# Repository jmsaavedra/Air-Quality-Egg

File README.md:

# Air Quality Egg

A large-scale distributed air quality network sensor device. based on the Nanode
an Arduino-compatible, Ethernet enabled microcontroller.
[airqualityegg.com](http://airqualityegg.com)

## Sensors
* temp/humidity (RHT22)
* carbon monoxide (e2v MICS-5525)
* nitrous dioxide (e2v MICS-2710)

## Notes
* auto reset feature connects digitalPin 3 to RESET pin
** this *must* be disconnected when programming the board.

## Collaborators
* [cosm.com](http://cosm.com)
* [citizensensor.cc](http://citizensensor.cc) | [jos.ph](http://jos.ph)
* [Wicked Device](http://wickeddevice.com)
* Ricardo Piedrahita, Nick Masson - UC Boulder (-link-)
* your name here

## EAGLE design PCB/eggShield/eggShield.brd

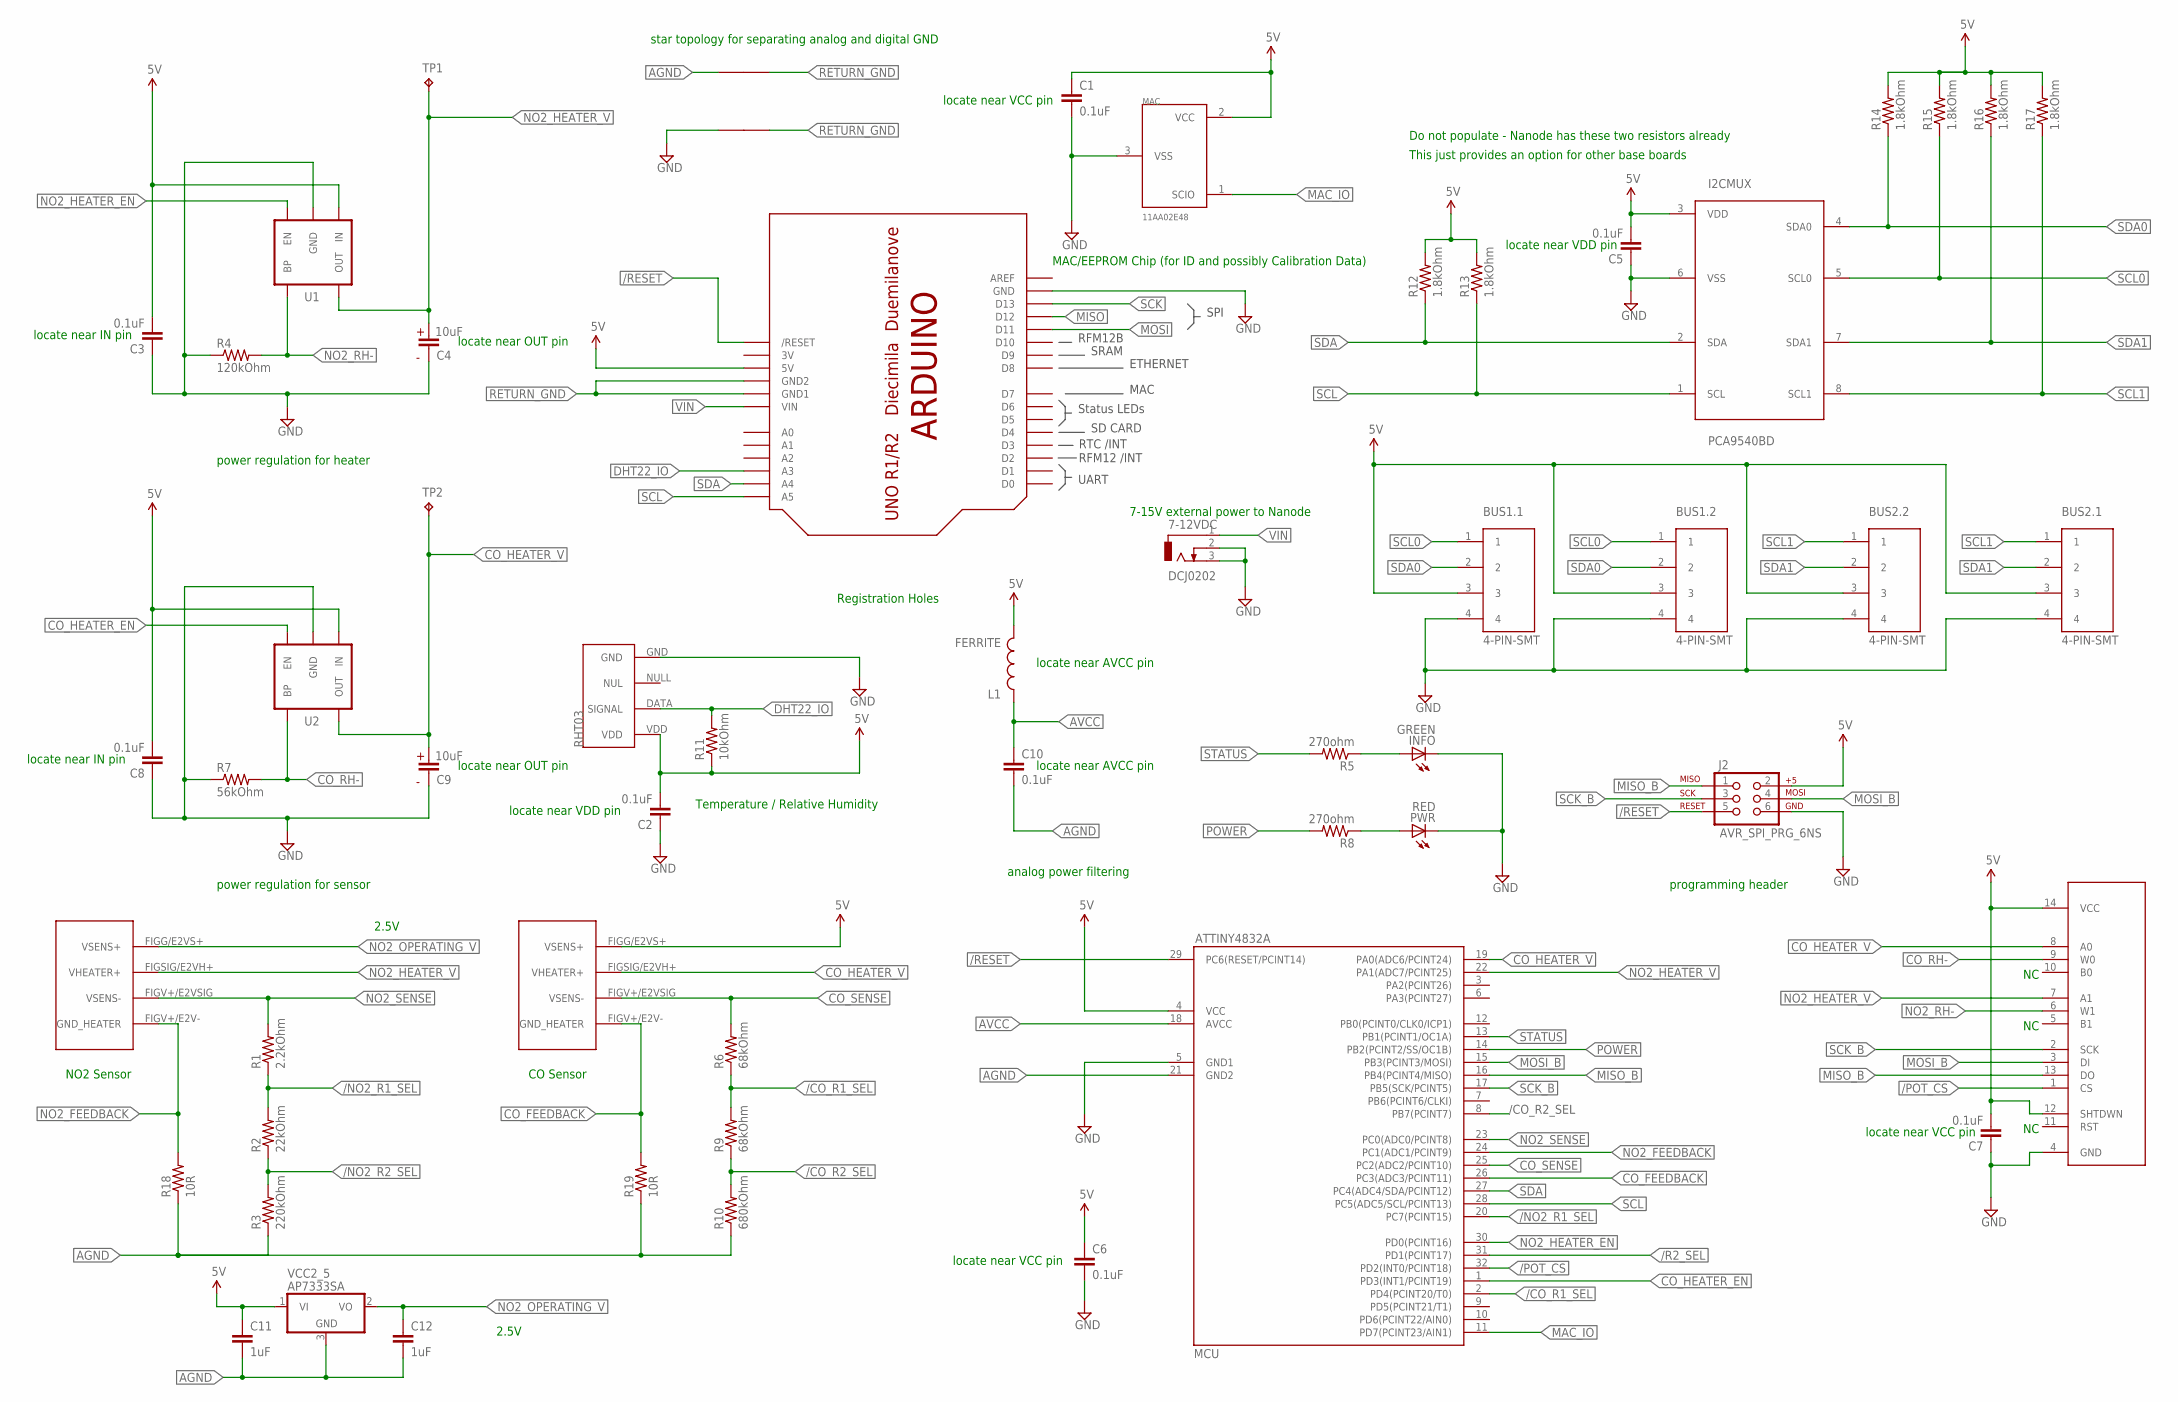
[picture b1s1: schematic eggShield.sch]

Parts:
7-12VDC: DCJ0202
BUS1.1, BUS1.2, BUS2.1, BUS2.2: 4-PIN-SMT; 1775470-4
C1, C2, C3, C5, C6, C7, C8, C10: 0.1uF; 0805
C4, C9: 10uF; TYPE-B_ALUMINUM_CAN
C11, C12: 1uF; 0805
CO: E2V; SR-4
DHT22: RHT03; 1X04_LOCK
I2CMUX: PCA9540BD; SO8
INFO: GREEN; CHIPLED_0805
J2: AVR_SPI_PRG_6NS; 2X3-NS
L1: FERRITE; 0805
MAC: 11AA02E48; SOT23
MCU: ATTINY4832A; TQFP32-08
N02: E2V; SR-4
PWR: RED; CHIPLED_0805
R1: 2.2kOhm; 0805
R2: 22kOhm; 0805
R3: 220kOhm; 0805
R4: 120kOhm; 0805
R5, R8: 270ohm; 0805
R6, R9: 68kOhm; 0805
R7: 56kOhm; 0805
R10: 680kOhm; 0805
R11: 10kOhm; 0805
R12, R13, R14, R15, R16, R17: 1.8kOhm; 0805
R18, R19: 10R; 0805
TP1, TP2: TPPAD1-13; P1-13
U1, U2: V_REG_LDOSMD; SOT23-5
U3: MCP42XXX; SO014
U$7: ARDUINO-NOHOLE
U$13, U$14: PLANE_COUPLER
VCC2_5: AP7333SA; SOT-23-3

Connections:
3V: U$7.3V
5V: BUS1.1.3, BUS1.2.3, BUS2.1.3, BUS2.2.3, C1.1, C2.2, C3.2, C5.2, C6.1, C7.2, C8.2, C11.1, CO.FIGG/E2VS+ (VSENS+), DHT22.VDD, I2CMUX.3 (VDD), J2.2, L1.2, MAC.2 (VCC), MCU.4 (VCC), R11.1, R12.2, R13.2, R14.2, R15.2, R16.2, R17.2, U1.1 (IN), U2.1 (IN), U3.12 (SHTDWN), U3.14 (VCC), U$7.5V, VCC2_5.1 (VI)
/CO_R1_SEL: MCU.2 (PD4(PCINT20/T0)), R6.1, R9.2
/CO_R2_SEL: MCU.8 (PB7(PCINT7)), R9.1, R10.2
/NO2_R1_SEL: MCU.20 (PC7(PCINT15)), R1.1, R2.2
/NO2_R2_SEL: R2.1, R3.2
/POT_CS: MCU.32 (PD2(INT0/PCINT18)), U3.1 (CS)
/R2_SEL: MCU.31 (PD1(PCINT17))
/RESET: J2.5, MCU.29 (PC6(RESET/PCINT14)), U$7.RESET (/RESET)
AGND: C10.2, C11.2, C12.2, MCU.21 (GND2), R3.1, R10.1, R18.1, R19.1, U$13.1, VCC2_5.3 (GND)
AVCC: C10.1, L1.1, MCU.18 (AVCC)
CO_FEEDBACK: CO.FIGV+/E2V- (GND_HEATER), MCU.26 (PC3(ADC3/PCINT11)), R19.2
CO_HEATER_EN: MCU.1 (PD3(INT1/PCINT19)), U2.3 (EN)
CO_HEATER_V: C9.P$1 (1), CO.FIGSIG/E2VH+ (VHEATER+), MCU.19 (PA0(ADC6/PCINT24)), TP2.TP, U2.5 (OUT), U3.8 (A0)
CO_RH-: R7.2, U2.4 (BP), U3.9 (W0)
CO_SENSE: CO.FIGV+/E2VSIG (VSENS-), MCU.25 (PC2(ADC2/PCINT10)), R6.2
DHT22_IO: DHT22.DATA (SIGNAL), R11.2, U$7.A3
GND: 7-12VDC.2, 7-12VDC.3, BUS1.1.4, BUS1.2.4, BUS2.1.4, BUS2.2.4, C1.2, C2.1, C3.1, C4.P$2 (2), C5.1, C6.2, C7.1, C8.1, C9.P$2 (2), DHT22.GND, I2CMUX.6 (VSS), INFO.C, J2.6, MAC.3 (VSS), MCU.5 (GND1), PWR.C, R4.1, R7.1, U1.2 (GND), U2.2 (GND), U3.4 (GND), U$7.GND, U$14.1
MAC_IO: MAC.1 (SCIO), MCU.11 (PD7(PCINT23/AIN1))
MISO: U$7.D12
MISO_B: J2.1, MCU.16 (PB4(PCINT4/MISO)), U3.13 (DO)
MOSI: U$7.D11
MOSI_B: J2.4, MCU.15 (PB3(PCINT3/MOSI)), U3.3 (DI)
unnamed: INFO.A, R5.1
unnamed: PWR.A, R8.1
NO2_FEEDBACK: MCU.24 (PC1(ADC1/PCINT9)), N02.FIGV+/E2V- (GND_HEATER), R18.2
NO2_HEATER_EN: MCU.30 (PD0(PCINT16)), U1.3 (EN)
NO2_HEATER_V: C4.P$1 (1), MCU.22 (PA1(ADC7/PCINT25)), N02.FIGSIG/E2VH+ (VHEATER+), TP1.TP, U1.5 (OUT), U3.7 (A1)
NO2_OPERATING_V: C12.1, N02.FIGG/E2VS+ (VSENS+), VCC2_5.2 (VO)
NO2_RH-: R4.2, U1.4 (BP), U3.6 (W1)
NO2_SENSE: MCU.23 (PC0(ADC0/PCINT8)), N02.FIGV+/E2VSIG (VSENS-), R1.2
POWER: MCU.14 (PB2(PCINT2/SS/OC1B)), R8.2
RETURN_GND: U$7.GND1, U$7.GND2, U$13.2, U$14.2
SCK: U$7.D13
SCK_B: J2.3, MCU.17 (PB5(SCK/PCINT5)), U3.2 (SCK)
SCL: I2CMUX.1 (SCL), MCU.28 (PC5(ADC5/SCL/PCINT13)), R13.1, U$7.A5
SCL0: BUS1.1.1, BUS1.2.1, I2CMUX.5 (SCL0), R15.1
SCL1: BUS2.1.1, BUS2.2.1, I2CMUX.8 (SCL1), R17.1
SDA: I2CMUX.2 (SDA), MCU.27 (PC4(ADC4/SDA/PCINT12)), R12.1, U$7.A4
SDA0: BUS1.1.2, BUS1.2.2, I2CMUX.4 (SDA0), R14.1
SDA1: BUS2.1.2, BUS2.2.2, I2CMUX.7 (SDA1), R16.1
STATUS: MCU.13 (PB1(PCINT1/OC1A)), R5.2
VIN: 7-12VDC.1, U$7.VIN

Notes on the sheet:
power regulation for heater
NO2 Sensor
10uF
power regulation for sensor
locate near IN pin
locate near OUT pin
CO Sensor
Temperature / Relative Humidity
locate near VDD pin
Do not populate - Nanode has these two resistors already
This just provides an option for other base boards
SPI
SRAM
ETHERNET
SD CARD
MAC
Status LEDs
RFM12B
UART
Registration Holes
locate near VCC pin
star topology for separating analog and digital GND
locate near AVCC pin
analog power filtering
2.5V
programming header
7-15V external power to Nanode
RFM12 /INT
RTC /INT
MAC/EEPROM Chip (for ID and possibly Calibration Data)

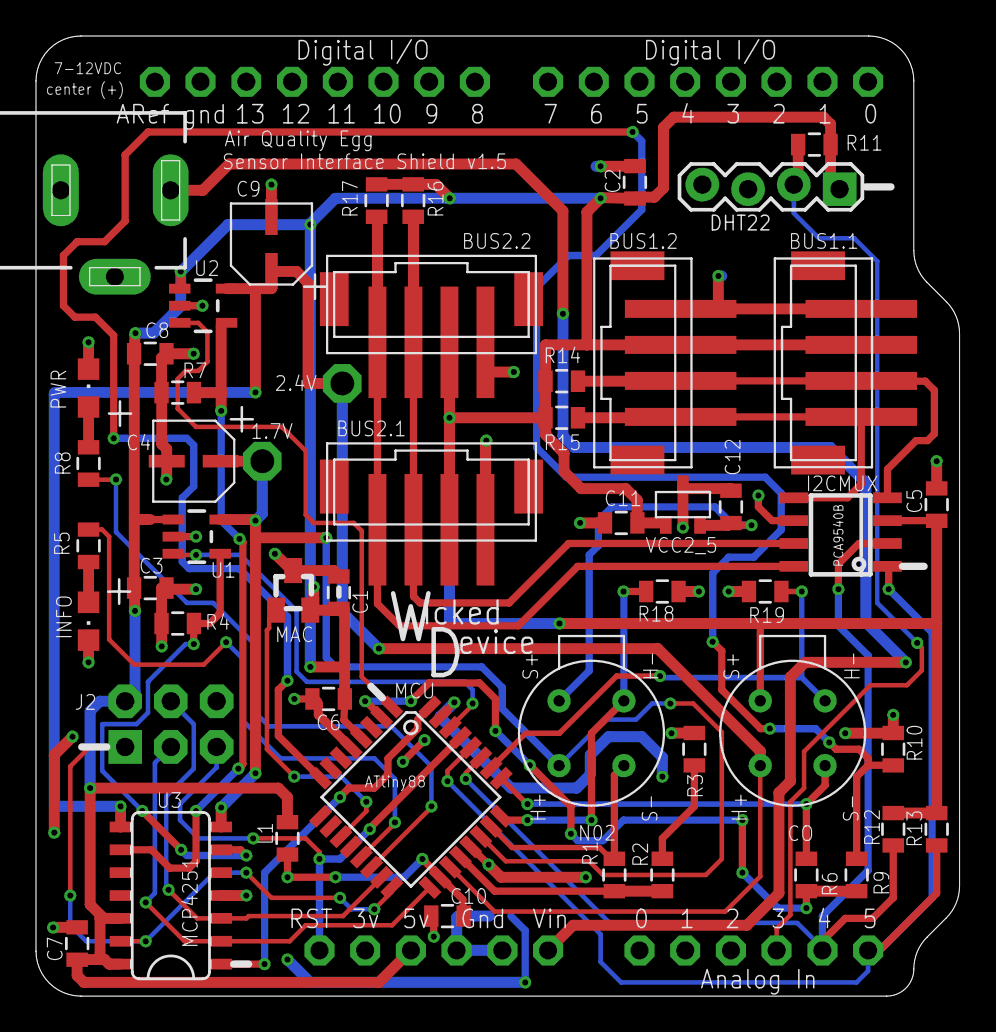
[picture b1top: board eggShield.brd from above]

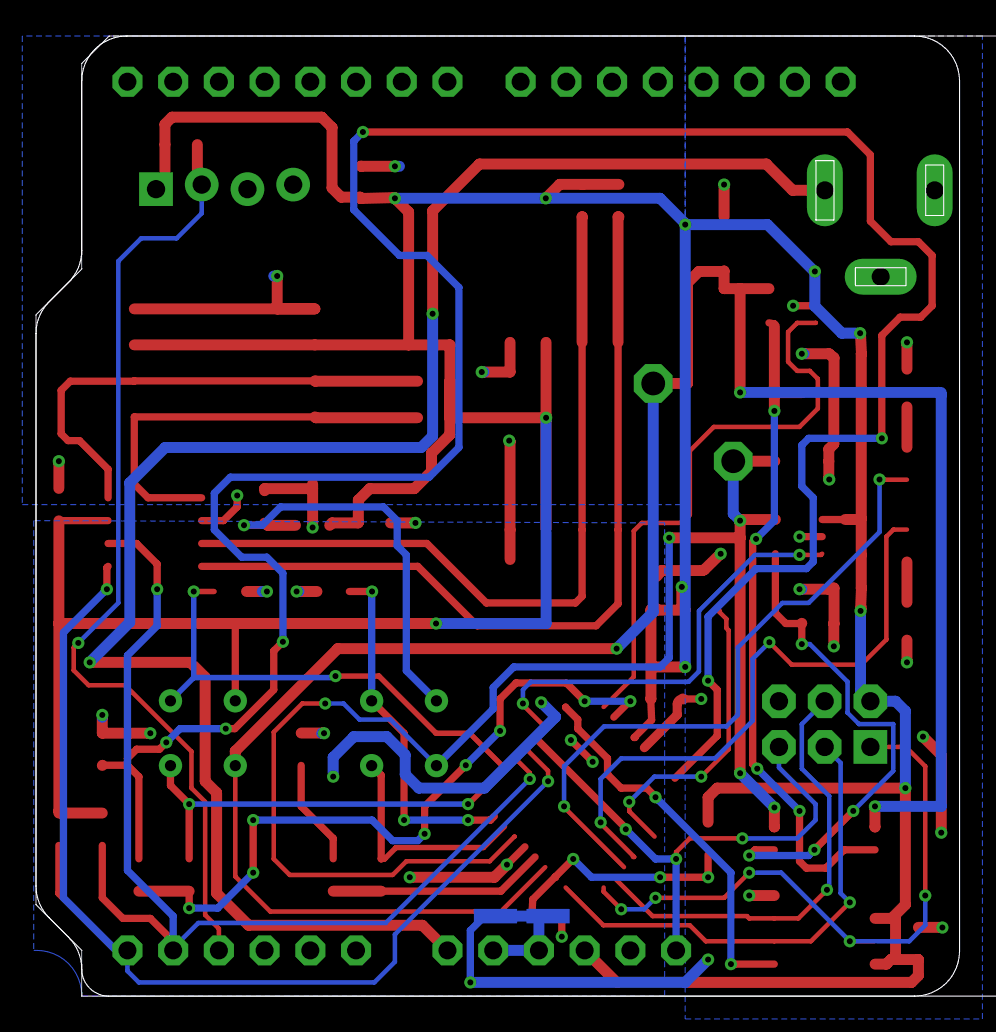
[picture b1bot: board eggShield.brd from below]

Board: 2 copper layers, 51.3 x 53.3 mm, 55 parts (2 on the bottom side), 38 nets.

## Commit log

2012-02-14 rename
2012-02-14 cleanup
2012-02-15 removed delays, added last successful transmit timer
2012-02-16 added reset timer
2012-02-16 clean up
2012-02-18 timing updates
2012-02-18 mq7 library github link
2012-02-28 refresh sync
2012-02-29 comments, readme
2012-02-29 readme
2012-04-07 added PCB files, workshop code
2012-04-08 added .brd, cleaned up
2012-04-08 cleaned board
2012-04-09 fixed RHT pin
2012-04-09 cleaned up a bit
2012-05-08 updated sensor circuit, removed unneeded compnts
2012-05-09 cleaned power circuit
2012-05-09 sensor update, needs i2c bus
2012-05-09 cleaned up
2012-05-09 added text
2012-05-09 added pdfs
2012-05-25 updates to the layout and schematics, bringing in elements of the CMOS breakout module
2012-05-26 added 2:1 I2C Multiplexer
2012-05-26 rearranged some layout and routing to improve power filtering
2012-05-27 some minor changes to component placement, routing, and silk screen
2012-05-27 added 4-pin connectors, needs to be checked against cabling; also noticed the range selection resistor taps need to be routed to arduino pins as well
2012-05-28 added routing for range select signals to arduino header and updated silkscreen for e2v sensors
2012-05-28 changed DHT22 I/O to DIG2, changed LDO feedback resistor values again, added more documentation to the schematic
2012-05-28 added registration holes
2012-05-28 adding solderpad schematic and board images
2012-06-03 major changes incorporating a heater co-processor
2012-06-12 updated images for solderpad
2012-06-14 incorporated several changes based on review comments
2012-06-15 updated to make it possible to shut down heaters from coprocessor, added programming header, added analog inputs to measure heater V+, and moved /R2_SEL to accomodate
2012-06-15 fixed a couple sloppy routes
2012-06-20 added barrel jack to shield for 7-15V external power to NAnode
2012-06-20 added silk screen to barrel jack to make voltage input range and polarity clear
2012-06-20 deleted registration hole that was sitting out in the middle of nowhere
2012-07-05 routed DHT22 to A3
2012-07-05 updated solderpad images
2012-07-16 fixed 2.5v regulator bug
2012-07-16 picked a more direct route for the 2.5v bug fix
2012-08-08 updates to the initial prototype based on testing and feedback. Fixed crossed up digipot lines, rotated the DHT22, move the barrel jack off the headers, replaced 0603s with 0805s.
2012-08-08 masked vias
2012-09-08 production version
2012-10-10 adding libraries
2012-11-09 updated the library to provide real units through table interpolation and added more examples
2012-11-11 fixed some bugs in the interpolation code for getSensorValue
2012-11-14 added supplemental libraries
2012-11-14 updated to latest ethercard library @jcw 1c465ca003d8a3d429fe4cc8e1fc01ae4576377d
2012-11-17 adding sketch for single Nanode + Shield AQE sketch v1
2012-11-17 added NanodeMAC
2012-11-17 adding sha library
2012-11-17 changed write test values to the defaults we program with
2012-11-17 added separate base and remote sketches
2012-11-17 adding JeeLib library
2012-11-18 switched to json
2012-11-20 increased ethernet buffer size, improved stability
2012-11-21 RGB library for the UI Shield
2012-11-21 made base station pairing behavior non-blocking for the sake of RGB control
2012-11-21 updated Base sketch to yellow glow the RGB led during pairing
2012-11-21 added single bounce capability
2012-11-21 updated rgb led behavior slightly
2012-11-21 added more RGB status indication
2012-11-21 accidentally checked in a test condition
2012-12-03 Updated some references from Pachube -> Cosm.
    * updated readme
    * updated api key header name in AQEBase, AQEBaseSensor, and
    AirQualityEggNanode. Didn't change any of the references in the dev or
    AQEWkshop directories or any examples in contained libraries.
2012-12-05 AQEBaseSensor appears to be constructing JSON not CSV.
    This means data should be sent to the JSON endpoint. Clearly this has
    been working and will continue to work probably, but is incorrect so
    should be updated. The alternative to specifying the content type in the
    URL would be to add an "Accept: application/json" header.
2012-12-10 fixed base sensor sketch
2012-12-10 updated firmware version, welcome message, and added shield firmware version to tags
2012-12-10 added firmware version tag
2012-12-11 forgot to return a value for getFirmwareVersion
2013-01-04 fixed negative value bug in radio link sensor value
2013-01-04 rolled version number information, put some strings in flash in the Remote code to save RAM
2013-01-26 fixed provisioning bug
2013-01-29 fixed bug in extrapolation in EggBus library getSensorValue method that was resulting in 0/0 divisions
2013-01-29 rolled version of Base Sensor sketch to note EggBus library changed
2013-01-30 updated sensor polling loop in Remote Egg to fix missing raw values
2013-02-03 added more expressive RGB LED feedback to the startup / initialization process, including pairing feedback
2013-02-05 added check for cosm reply, improved stability
2013-02-05 rolled AQEBaseSensor version number to 1.09
2013-02-06 update to auto reset at regular intervals for Wired Base
2013-02-07 separated provisioning from sensor reporting for Wired Egg System
2013-02-07 file got lost in the shuffle, putting it back in
2013-02-07 added zero-crossing fix to EggBus, rolled versions
2013-02-15 added code for SD logger version
2013-02-15 added SD logger version
2013-03-18 added update to the eggbus lib to enable logger shield
2013-03-18 added binaries and load scripts
2013-04-30 added function to retrieve the ADC value and selected low side resistance
2013-05-07 updated to 2.0 egg bus interface per may 6th blog post at blog.wickeddevice.com
2013-05-08 updated version number strings and load binaries
2013-05-24 updated EggBus examples to use the 2.0 API
2013-05-31 updated softwares to fix problem with provisioning now that xively creates long feed-ids (up to 10 digits), also fixed a minor bug in reporting sensor type for raw feeds on Egg Base sketch
2013-05-31 renamed hex file
2013-06-04 cosm timeout interval was too short for eggs containng add ons
2013-06-04 rolled the version number
2013-06-04 adding updated binary file
2013-06-10 Example for using AQERemote and AQEShield with standard openenergymonitor RF packet format
2014-04-14 added watchdog timer code and updated to most recent EtherCard library code
2014-04-14 updated hex file
2014-04-25 added fallback to static IP if DNS lookup fails, bumped reported version to 2.03
2014-04-25 added DNS fail fallback to static IP for Xivly for alternative Egg (Wired Only) configuration
2014-04-25 updated hex files and updated remote to not return instantly on pairing success and to send data right after pairing interval completes
2014-04-25 better eeprom handling in Egg Remote
2014-05-07 disallow negative values returned by the EggBus library - report them as zero
2015-08-23 Converts Readme to markdown
    Converts Readme to markdown and formats so URLs work on GH

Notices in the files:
parts and their libraries:
SparkFun: Licensing: CC v3.0 Share-Alike You are welcome to use this library for commercial purposes.
